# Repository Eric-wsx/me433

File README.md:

# hello-world
get started with the github
// learn how to use the repository
// edit the new branch

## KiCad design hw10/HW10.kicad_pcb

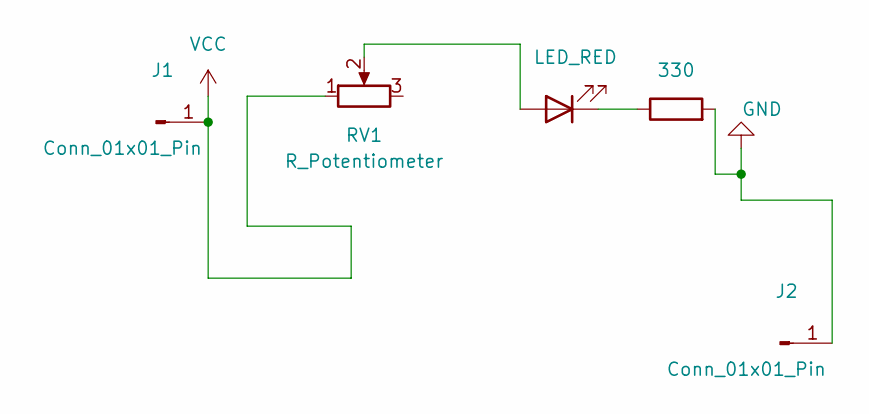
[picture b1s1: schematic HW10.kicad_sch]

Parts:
D2: LED_RED; LED_D3.0mm_FlatTop
J1: Conn_01x01_Pin; PinHeader_1x01_P1.27mm_Vertical
J2: Conn_01x01_Pin; PinHeader_1x01_P1.27mm_Horizontal
R1: 330; R_Array_SIP5
RV1: R_Potentiometer; Potentiometer_ACP_CA6-VSMD_Vertical

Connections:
GND: J2.1, R1.2
unnamed: D2.2 (A), RV1.2
unnamed: D2.1 (K), R1.1
VCC: J1.1, RV1.1

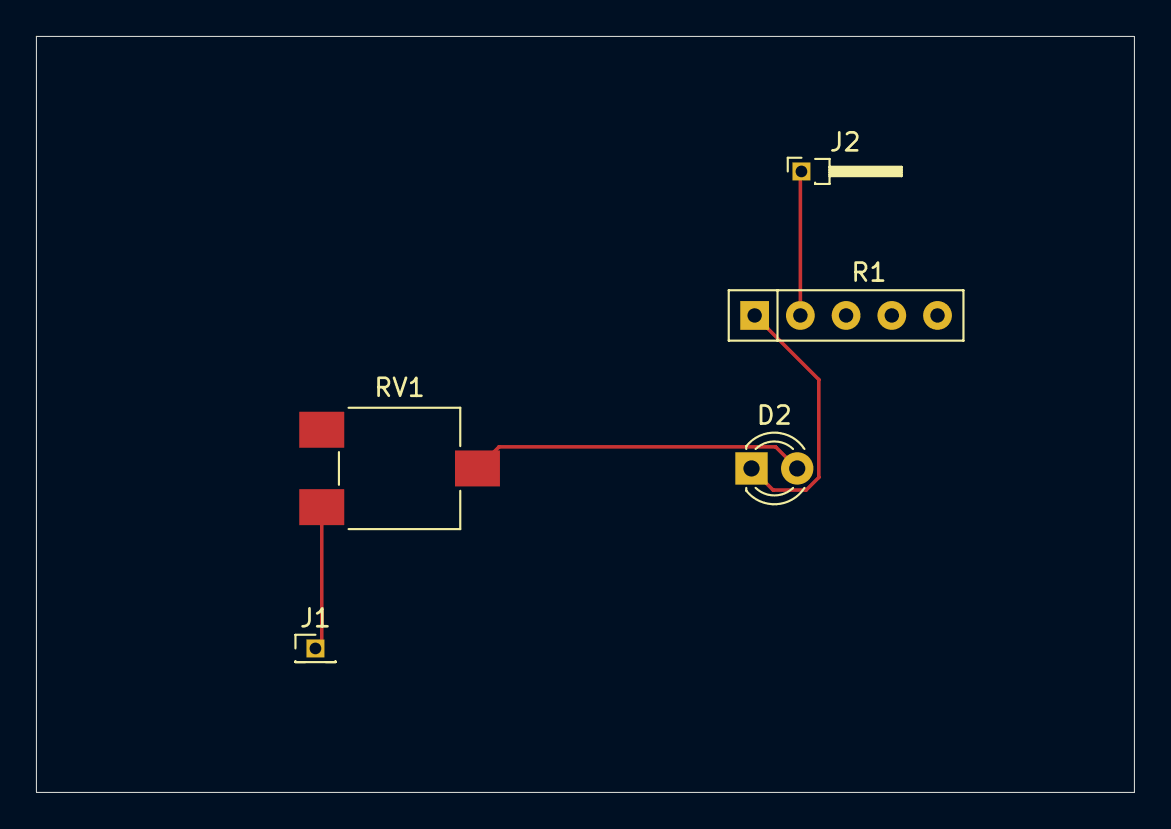
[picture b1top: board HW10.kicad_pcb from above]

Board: 2 copper layers, 61.0 x 42.0 mm, 5 parts (0 on the bottom side), 4 nets.

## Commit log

2024-01-11 Update README.md
    This is used to try to edit the branch and commit changes.
2024-04-12 hw2 hw3 hw4
2024-05-25 hw12 and hw14
2024-05-27 hw15
2024-05-29 finish 10 11 16
2024-05-29 hw10
